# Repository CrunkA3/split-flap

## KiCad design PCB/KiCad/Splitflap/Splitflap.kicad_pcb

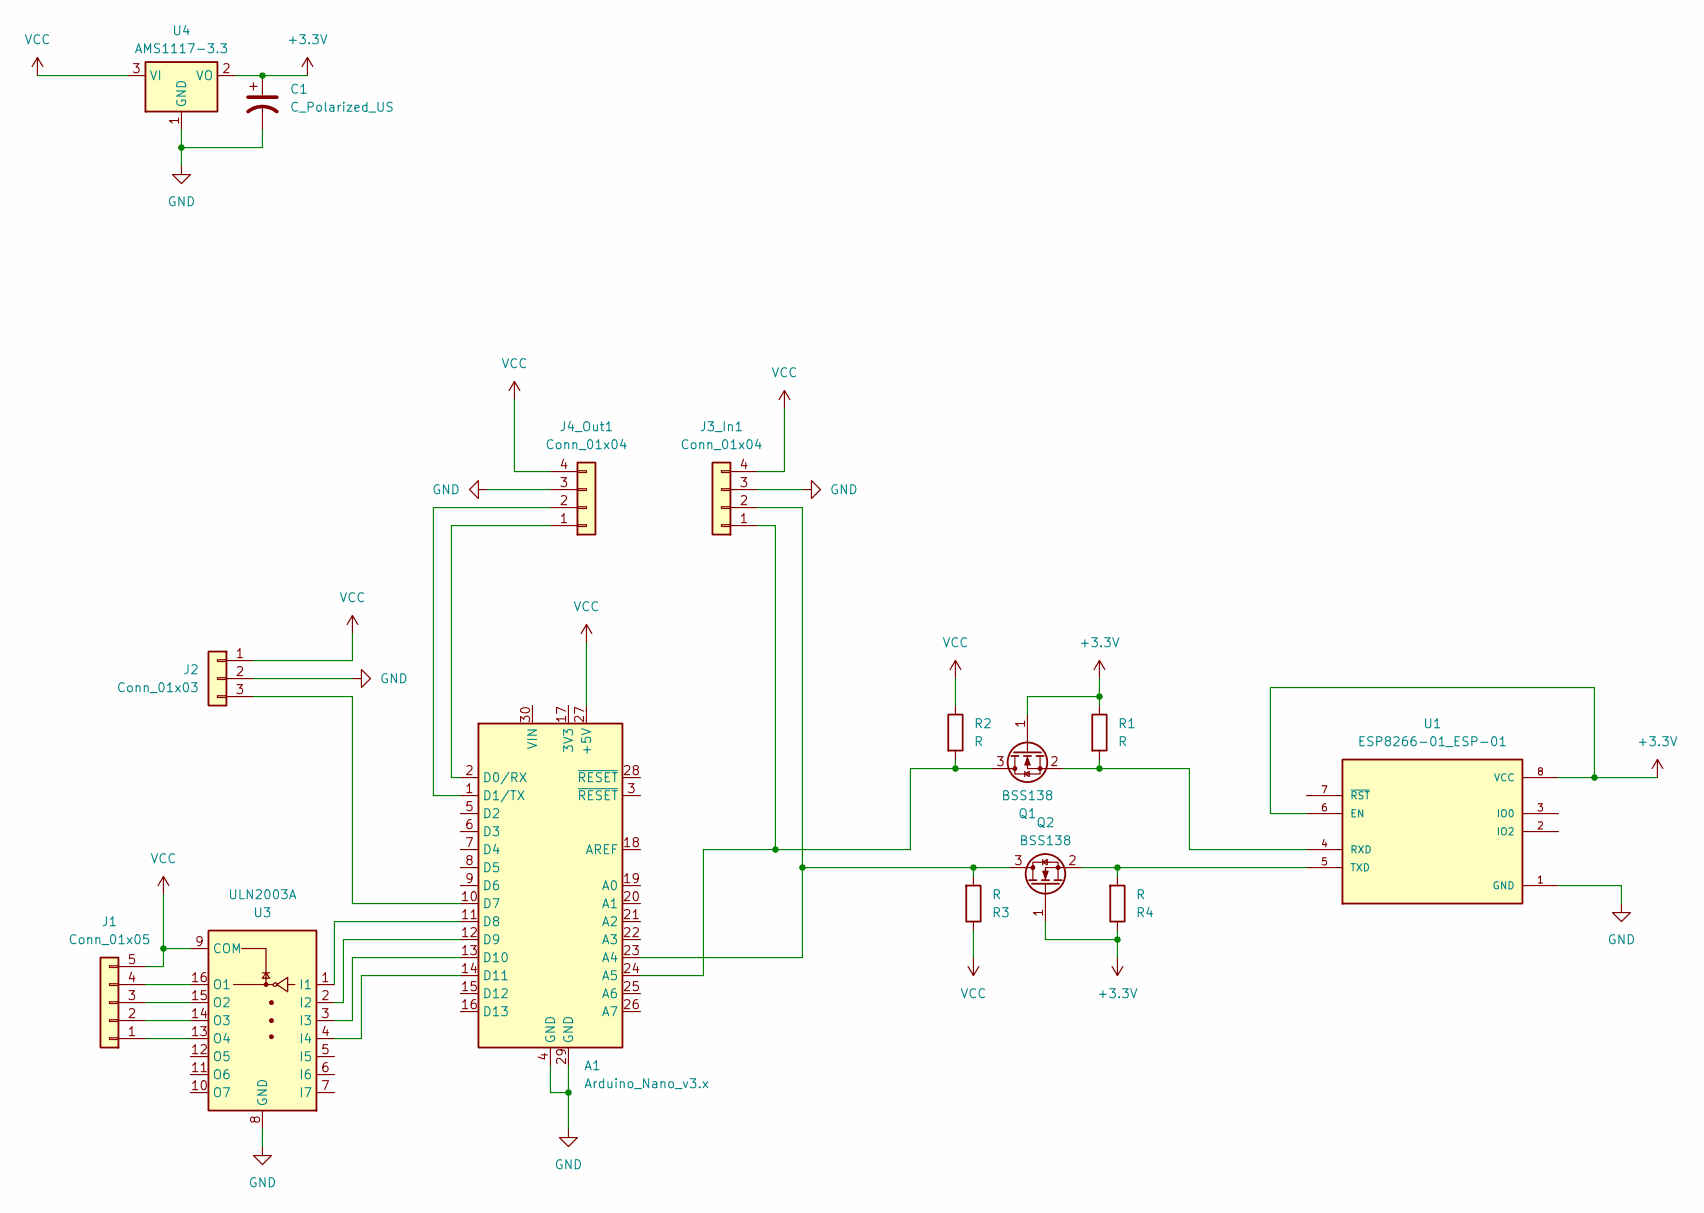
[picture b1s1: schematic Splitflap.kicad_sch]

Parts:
A1: Arduino_Nano_v3.x; Arduino_Nano
C1: C_Polarized_US; CP_Radial_D4.0mm_P2.00mm
J1: Conn_01x05; JST_XH_B5B-XH-AM_1x05_P2.50mm_Vertical
J2: Conn_01x03; JST_XH_B3B-XH-AM_1x03_P2.50mm_Vertical
J3_In1, J4_Out1: Conn_01x04; JST_XH_B4B-XH-AM_1x04_P2.50mm_Vertical
Q1, Q2: BSS138; SOT-23
R1, R2, R3, R4: R; R_Axial_DIN0204_L3.6mm_D1.6mm_P1.90mm_Vertical
U1: ESP8266-01_ESP-01; ESP-01; PARTREV V1.2
U3: ULN2003A; DIP-16_W7.62mm
U4: AMS1117-3.3; SOT-223-3_TabPin2

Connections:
+3.3V: C1.1, Q1.1 (G), Q2.1 (G), R1.1, R4.1, U1.6 (EN), U1.8 (VCC), U4.2 (VO)
GND: A1.4 (GND), A1.29 (GND), C1.2, J2.2, J3_In1.3, J4_Out1.3, U1.1 (GND), U3.8 (GND), U4.1 (GND)
unnamed: A1.23 (A4), J3_In1.2, Q2.3 (D), R3.2
unnamed: A1.24 (A5), J3_In1.1, Q1.3 (D), R2.2
unnamed: A1.2 (D0/RX), J4_Out1.1
unnamed: A1.1 (D1/TX), J4_Out1.2
unnamed: A1.10 (D7), J2.3
unnamed: A1.11 (D8), U3.1 (I1)
unnamed: A1.12 (D9), U3.2 (I2)
unnamed: A1.13 (D10), U3.3 (I3)
unnamed: A1.14 (D11), U3.4 (I4)
unnamed: J1.1, U3.13 (O4)
unnamed: J1.2, U3.14 (O3)
unnamed: J1.3, U3.15 (O2)
unnamed: J1.4, U3.16 (O1)
unnamed: Q1.2 (S), R1.2, U1.4 (RXD)
unnamed: Q2.2 (S), R4.2, U1.5 (TXD)
VCC: A1.27 (+5V), J1.5, J2.1, J3_In1.4, J4_Out1.4, R2.1, R3.1, U3.9 (COM), U4.3 (VI)

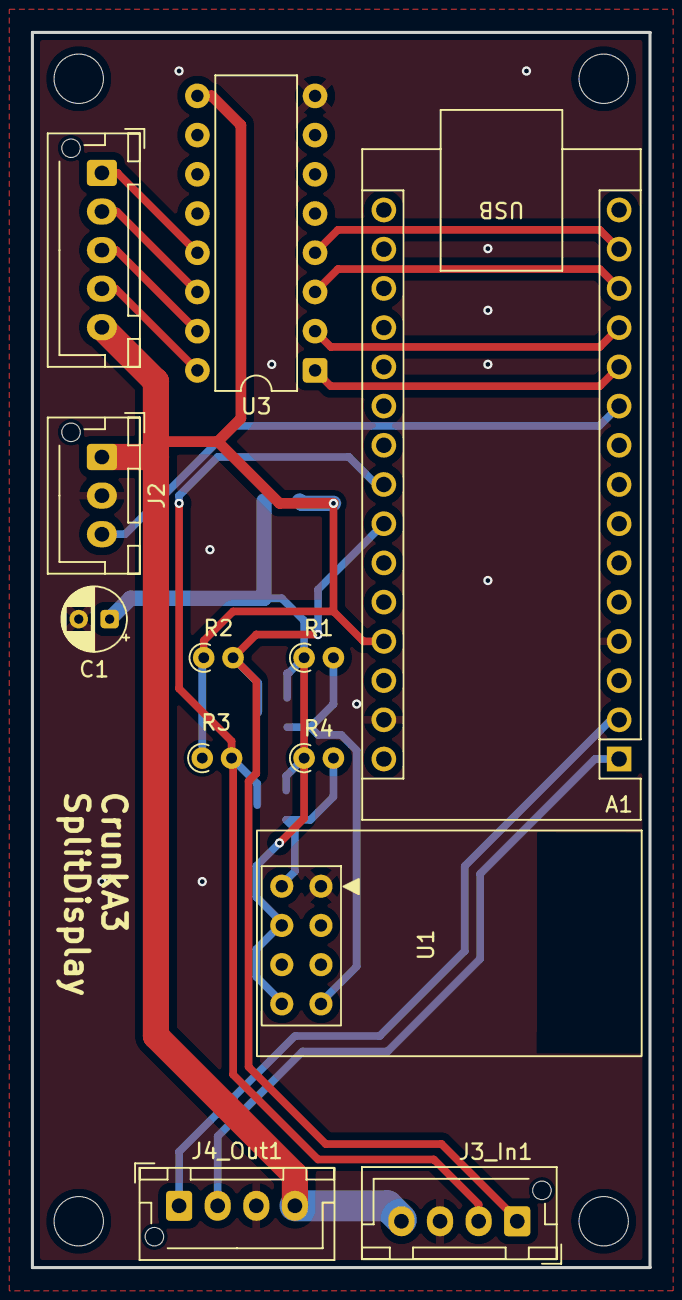
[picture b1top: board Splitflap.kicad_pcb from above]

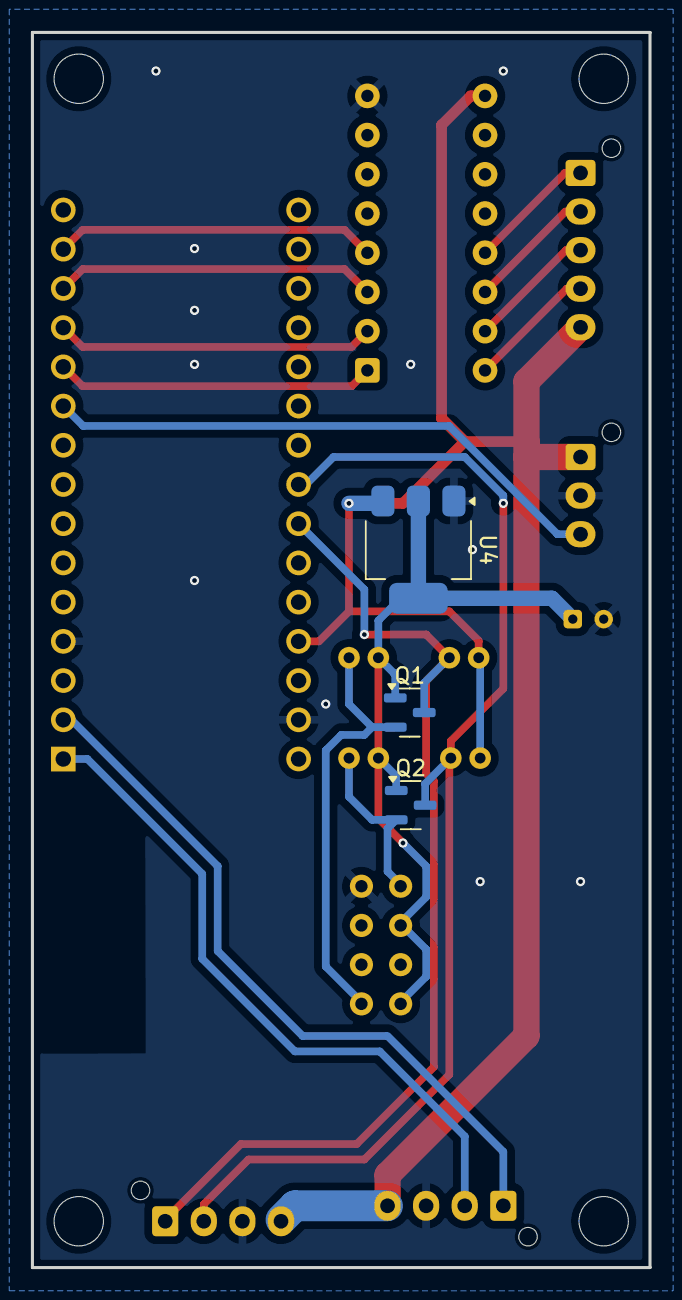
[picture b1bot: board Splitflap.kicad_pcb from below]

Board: 2 copper layers, 40.0 x 80.0 mm, 15 parts (3 on the bottom side), 18 nets.

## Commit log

2025-11-03 eigene Platine
2025-11-04 5v variante
2025-11-04 add gitignore
2025-11-19 add custom drums
2025-11-23 bigger flap holes
